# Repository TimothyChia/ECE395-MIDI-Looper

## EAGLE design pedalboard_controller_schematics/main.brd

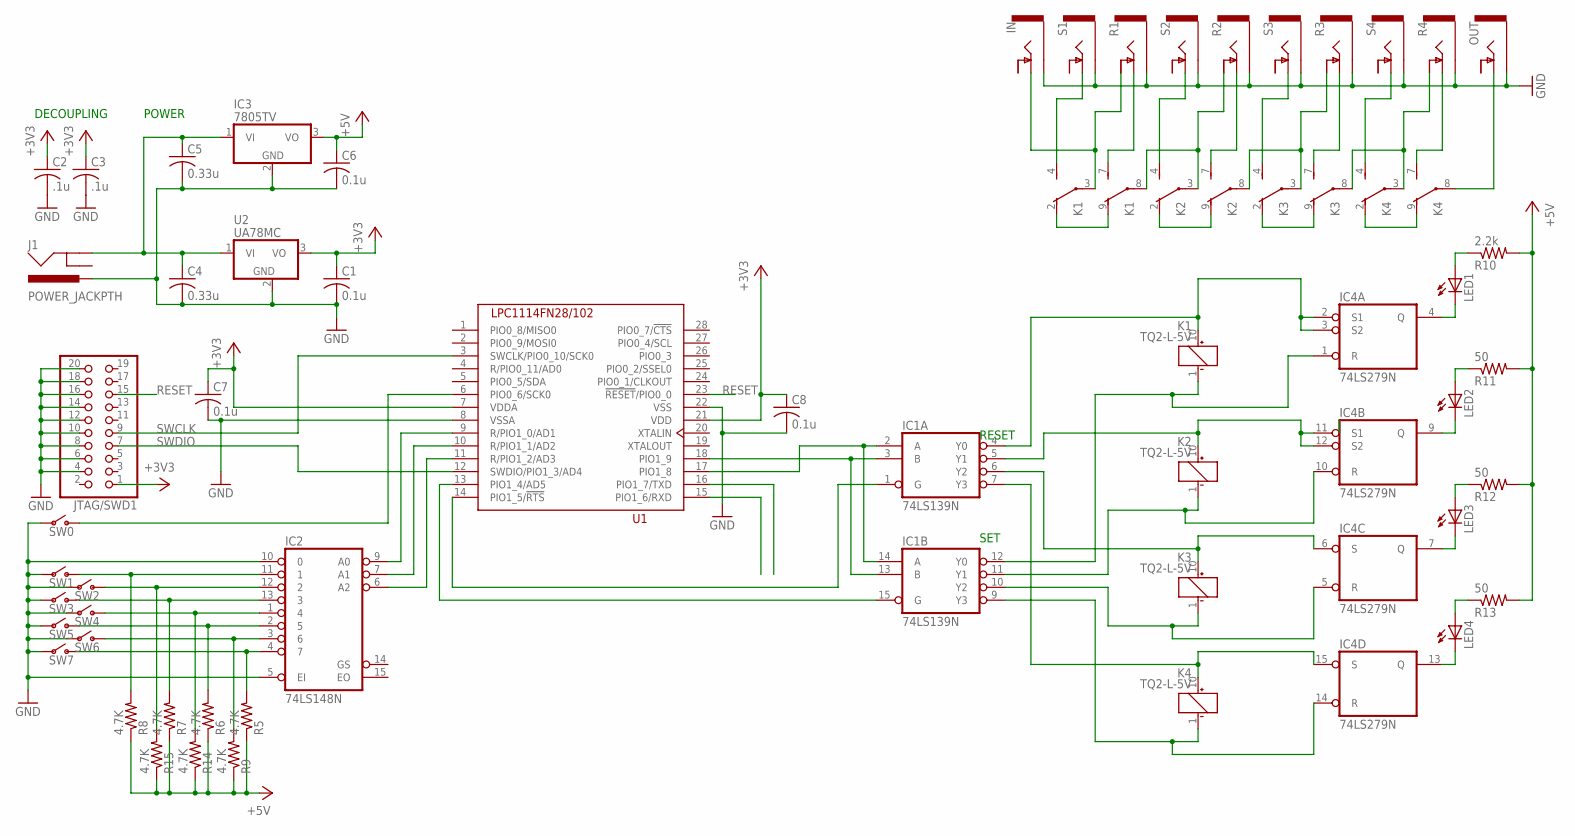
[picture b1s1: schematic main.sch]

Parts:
C1, C6, C7, C8: 0.1u; C050-024X044
C2, C3: .1u; C050-024X044
C4, C5: 0.33u; C050-024X044
IC1: 74LS139N; DIL16
IC2: 74LS148N; DIL16
IC3: 7805TV; TO220V
IC4: 74LS279N; DIL16
IN: AUDIO-JACK-NORM-TS; AUDIO-JACK-.25-INCH-SWCRAFT
J1: POWER_JACKPTH; POWER_JACK_PTH
JTAG/SWD1: PINHD-2X10; 2X10
K1, K2, K3, K4: TQ2-L-5V; TQ2
LED1, LED2, LED3, LED4: LED5MM
OUT: AUDIO-JACK-NORM-TS; AUDIO-JACK-.25-INCH-SWCRAFT
R1, R2, R3, R4: AUDIO-JACK-NORM-TS; AUDIO-JACK-.25-INCH-SWCRAFT
R5, R6, R7, R8, R9, R14, R15: 4.7K; 0204/7
R10: 2.2k; 0204/7
R11, R12, R13: 50; 0204/7
S1, S2, S3, S4: AUDIO-JACK-NORM-TS; AUDIO-JACK-.25-INCH-SWCRAFT
SW0, SW1, SW2, SW3, SW4, SW5, SW6, SW7: SWITCH-SPST; SWITCH_SPST_OFFBOARD
U1: LPC1114FN28/102; DIL28-6
U2: UA78MC; TO220V

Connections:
+3V3: C1.1, C2.1, C3.1, C7.1, C8.1, JTAG/SWD1.1, U1.7 (VDDA), U1.21 (VDD), U2.3 (VO)
+5V: C6.1, IC3.3 (VO), R5.1, R6.1, R7.1, R8.1, R9.1, R10.2, R11.2, R12.2, R13.2, R14.1, R15.1
GND: C1.2, C2.2, C3.2, C4.2, C5.2, C6.2, C7.2, C8.2, IC1.8 (GND), IC2.5 (EI), IC2.8 (GND), IC2.10 (0), IC3.2 (GND), IC4.8 (GND), IN.S, J1.PWR, JTAG/SWD1.4, JTAG/SWD1.6, JTAG/SWD1.8, JTAG/SWD1.10, JTAG/SWD1.12, JTAG/SWD1.14, JTAG/SWD1.16, JTAG/SWD1.18, JTAG/SWD1.20, OUT.S, R1.S, R2.S, R3.S, R4.S, S1.S, S2.S, S3.S, S4.S, SW0.3, SW1.3, SW2.3, SW3.3, SW4.3, SW5.3, SW6.3, SW7.3, U1.8 (VSSA), U1.22 (VSS), U2.2 (GND)
unnamed: C4.1, C5.1, IC3.1 (VI), J1.GND, U2.1 (VI)
unnamed: IC2.11 (1), R8.2, SW1.2
unnamed: IC1.3 (B), IC1.13 (B), U1.18 (PIO1_9)
unnamed: IC1.15 (G), U1.13 (PIO1_4/AD5)
unnamed: IC1.1 (G), U1.14 (PIO1_5/!RTS)
unnamed: IC1.10 (Y2), IC4.5 (R), K3.1 (-)
unnamed: IC1.4 (Y0), IC4.2 (S1), IC4.3 (S2), K1.10 (+)
unnamed: IC1.5 (Y1), IC4.11 (S1), IC4.12 (S2), K2.10 (+)
unnamed: IC1.11 (Y1), IC4.10 (R), K2.1 (-)
unnamed: IC1.6 (Y2), IC4.6 (S), K3.10 (+)
unnamed: IC1.7 (Y3), IC4.15 (S), K4.10 (+)
unnamed: IC1.9 (Y3), IC4.14 (R), K4.1 (-)
unnamed: IC1.12 (Y0), IC4.1 (R), K1.1 (-)
unnamed: IC4.4 (Q), LED1.K (C)
unnamed: IC4.9 (Q), LED2.K (C)
unnamed: IC4.7 (Q), LED3.K (C)
unnamed: IC4.13 (Q), LED4.K (C)
unnamed: LED1.A, R10.1
unnamed: LED2.A, R11.1
unnamed: LED3.A, R12.1
unnamed: LED4.A, R13.1
unnamed: IC1.2 (A), IC1.14 (A), U1.17 (PIO1_8)
unnamed: IC2.12 (2), R15.2, SW2.2
unnamed: IC2.13 (3), R7.2, SW3.2
unnamed: IC2.1 (4), R14.2, SW4.2
unnamed: IC2.2 (5), R6.2, SW5.2
unnamed: IC2.3 (6), R9.2, SW6.2
unnamed: IC2.4 (7), R5.2, SW7.2
unnamed: IN.T, K1.3, R1.TS
unnamed: K1.2 (O), K1.9 (O)
unnamed: K1.7 (S), R1.T
unnamed: K1.4 (S), S1.T
unnamed: K1.8, K2.3, R2.TS
unnamed: K2.2 (O), K2.9 (O)
unnamed: K2.4 (S), S2.T
unnamed: K2.7 (S), R2.T
unnamed: K2.8, K3.3, R3.TS
unnamed: K3.4 (S), S3.T
unnamed: K3.2 (O), K3.9 (O)
unnamed: K3.7 (S), R3.T
unnamed: IC2.9 (A0), U1.9 (R/PIO1_0/AD1)
unnamed: K3.8, K4.3, R4.TS
unnamed: K4.2 (O), K4.9 (O)
unnamed: K4.4 (S), S4.T
unnamed: K4.7 (S), R4.T
unnamed: IC2.7 (A1), U1.10 (R/PIO1_1/AD2)
unnamed: K4.8, OUT.T
unnamed: IC2.6 (A2), U1.11 (R/PIO1_2/AD3)
unnamed: SW0.2, U1.6 (PIO0_6/SCK0)
RESET: JTAG/SWD1.15, U1.23 (!RESET!/PIO0_0)
SWCLK: JTAG/SWD1.9, U1.3 (SWCLK/PIO0_10/SCK0)
SWDIO: JTAG/SWD1.7, U1.12 (SWDIO/PIO1_3/AD4)
VCC: IC1.16 (VCC), IC2.16 (VCC), IC4.16 (VCC)

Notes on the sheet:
POWER
DECOUPLING
SET
RESET

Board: 2 copper layers, 53 parts (0 on the bottom side), 56 nets, no tracks yet.

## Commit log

2017-03-30 LCD code
    initial move of the LCD code
2017-03-30 added schematic files
2017-03-30 Removed garbage
    removed the old draft
2017-03-30 Compilation related corrections
    someone needs to exclude the .o files
2017-03-30 Changes
    Make sure to read up on the AHBCLKCTRL register, page 34.
2017-03-31 Prototype Git-ignore from templates
    First attempt at ignoring uVision files, especially since we only have
    one copy of uVision.
2017-04-02 Serial Lines Working
    Enabled serial debugging
2017-04-04 Corrections to delay, removal of pin testing code.
    Pins are now all working correctly.
2017-04-04 Cleaning up crf files from git index
    Still don't really know how to use gitignore
2017-04-04 Clearing out the uVision files.
2017-04-04 debugging statements
    something is wrong with the bitwise negation of LCD_EN.
2017-04-06 Added main project pedalboard_controller
2017-04-06 Pullup Code
    Disabling pullups to use proper 5V logic
2017-04-11 Beginnings of relay config and relay initialization.
    Adapting to maintain similar structure to LCD driver.
2017-04-11 Relay Code
    Got the relays working. Placeholder files added, these need to be burst.
2017-04-12 modified eagle schematic
2017-04-13 updated schematic and code
2017-04-18 updated schematic
2017-04-18 added Sparkfun libraries
2017-04-19 Added parts to EAGLE libraries, added switching section in schematic
2017-04-25 fixed encoder section
2017-04-25 Prototype Code for footswitches and presets
2017-05-01 updated main board
2017-05-01 Code now works with hardware, debouncing added.
2017-05-02 finalized PCB

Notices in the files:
parts and their libraries:
SparkFun-Connectors: Licensing: Creative Commons ShareAlike 4.0 International - https://creativecommons.org/licenses/by-sa/4.0
